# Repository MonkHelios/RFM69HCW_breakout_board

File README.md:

# RFM69HCW_breakout_board
RFM69HCW breakout board PCB files and arduino library

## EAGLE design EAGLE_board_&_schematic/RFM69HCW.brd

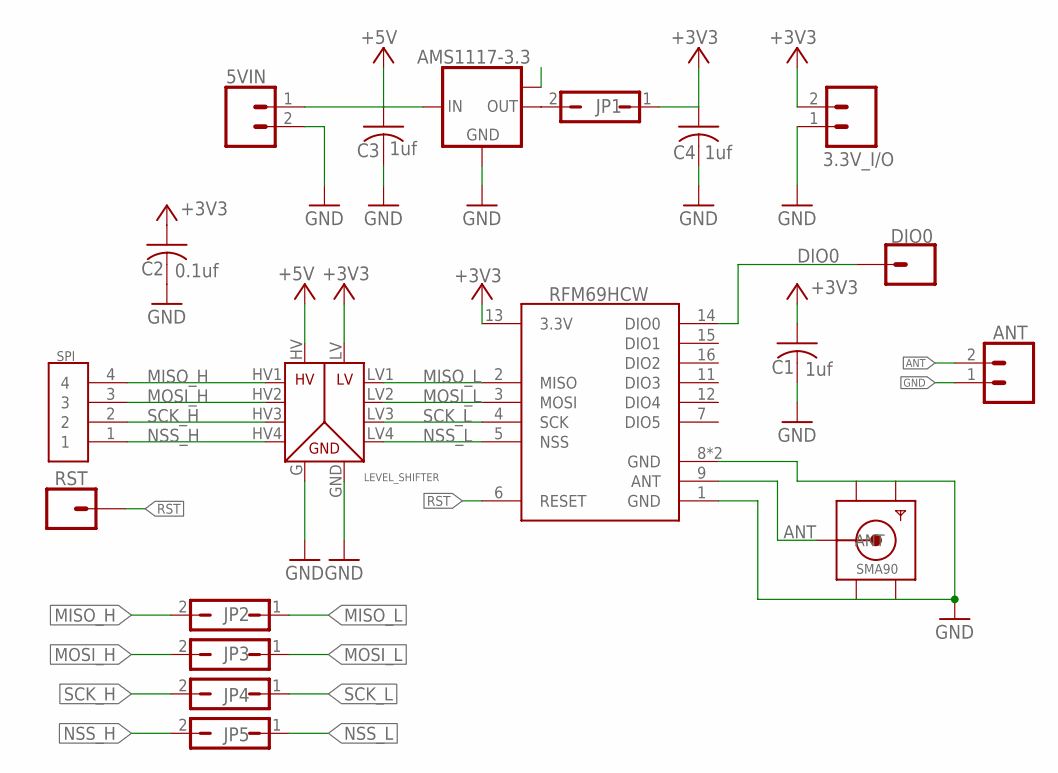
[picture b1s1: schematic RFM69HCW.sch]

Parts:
3.3V_I/O, 5VIN: M021X02_NO_SILK; 1X02_NO_SILK
AMS1117-3.3: LM1117MPX-1.8; SOT223
ANT: M021X02_NO_SILK; 1X02_NO_SILK
C1, C3, C4: 1uf; C0805
C2: 0.1uf; C0805
DIO0: M01SMDNS; 1X01NS
JP1, JP2, JP3, JP4, JP5: JP1Q; JP1
RST: M01SMDNS; 1X01NS
SMA90: SMACONNECTOR_EDGE; SMA_EDGELAUNCH
SPI: 1X4-CLEANBIG; 1X04-CLEANBIG
U1: RFM69HCW; RFM69HCW-XXXS2
U$1: LEVEL_SHIFTER

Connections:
+3V3: 3.3V_I/O.2, C1.1, C2.1, C4.1, JP1.1, U1.13 (3.3V), U$1.LV
+5V: 5VIN.1, AMS1117-3.3.3 (IN), C3.1, U$1.HV
ANT: ANT.2, SMA90.P (ANT), U1.9 (ANT)
DIO0: DIO0.1, U1.14 (DIO0)
GND: 3.3V_I/O.1, 5VIN.2, AMS1117-3.3.1 (GND), ANT.1, C1.2, C2.2, C3.2, C4.2, SMA90.GND@1 (GND4), SMA90.GND@2 (GND3), SMA90.GND@3 (GND2), SMA90.GND@4 (GND1), U1.1 (GND), U1.8 (GND), U1.10 (GND), U$1.G (GND), U$1.GND (GND1)
MISO_H: JP2.2, SPI.4, U$1.HV1
MISO_L: JP2.1, U1.2 (MISO), U$1.LV1
MOSI_H: JP3.2, SPI.3, U$1.HV2
MOSI_L: JP3.1, U1.3 (MOSI), U$1.LV2
unnamed: AMS1117-3.3.2 (OUT), JP1.2
NSS_H: JP5.2, SPI.1, U$1.HV4
NSS_L: JP5.1, U1.5 (NSS), U$1.LV4
RST: RST.1, U1.6 (RESET)
SCK_H: JP4.2, SPI.2, U$1.HV3
SCK_L: JP4.1, U1.4 (SCK), U$1.LV3

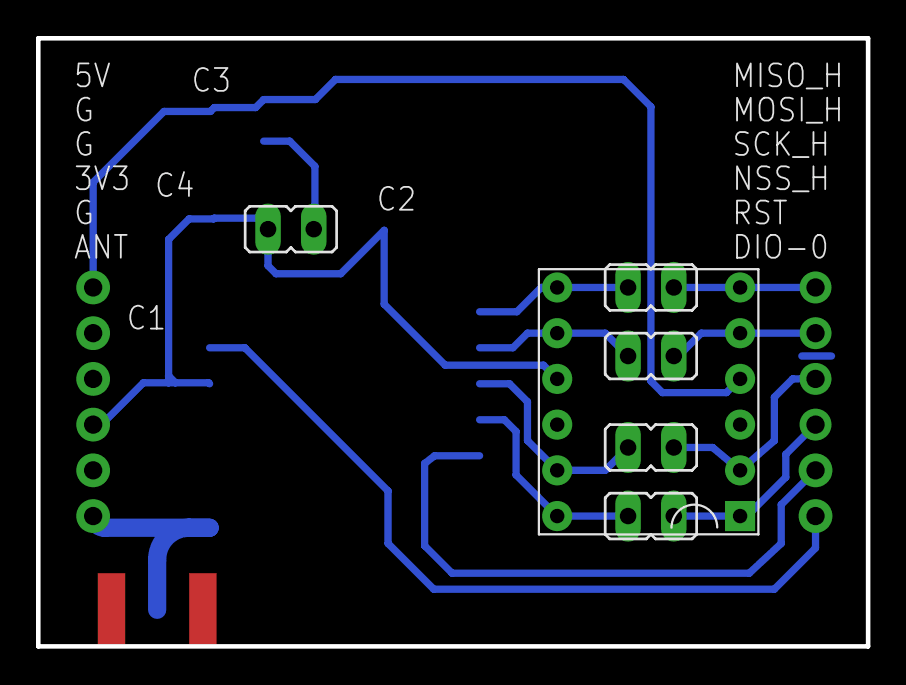
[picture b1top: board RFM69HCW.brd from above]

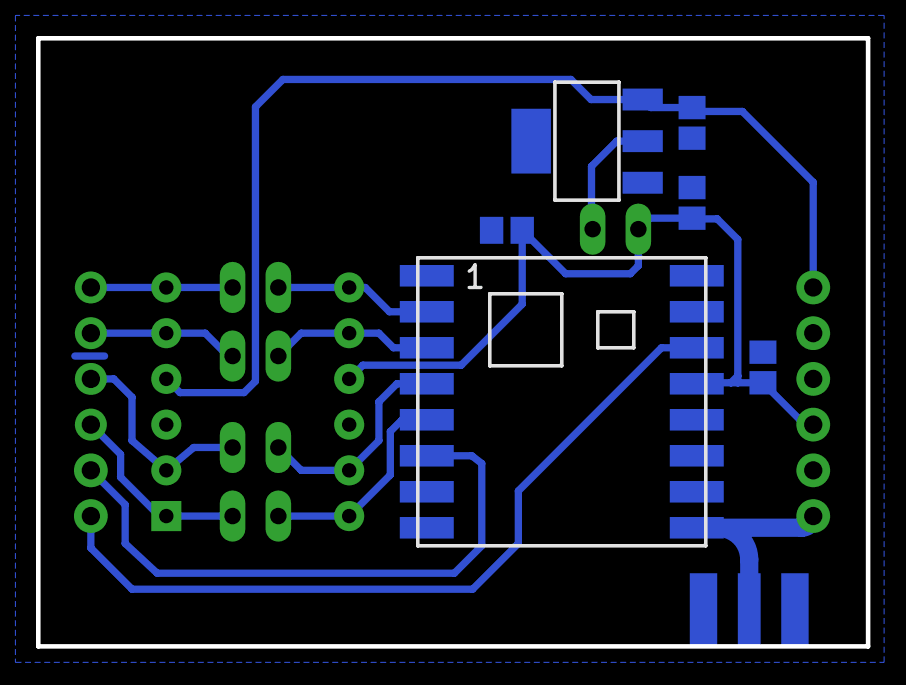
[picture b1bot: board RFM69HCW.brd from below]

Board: 2 copper layers, 46.1 x 33.8 mm, 19 parts (7 on the bottom side), 15 nets.

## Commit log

2018-04-20 new file: EAGLE_board_&_schematic/RFM69HCW.brd new file: EAGLE_board_&_schematic/RFM69HCW.sch new file: EAGLE_board_&_schematic/RFM69HCW_CKT.pdf new file: RFM69HCW_arduino/.travis.yml new file: RFM69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
2018-07-22 Move example sketches to appropriately named folder
    The Arduino IDE requires the sketch folder name to match the filename of the primary sketch file. This change causes the example sketch to be accessible via the Arduino IDE's File > Examples > LIBRAR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
    Reference:
    https://github.com/arduino/Arduino/wiki/Arduino-IDE-1.5:-Library-specification#library-examples

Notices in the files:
parts and their libraries:
SparkFun-Aesthetics: Licensing: CC v3.0 Share-Alike You are welcome to use this library for commercial purposes.
